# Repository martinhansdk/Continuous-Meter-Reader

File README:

Continuous Meter Reader
=======================

A little gadget that sits on your water or electricity meter and monitors it continuously.
The collected reading are presented on a mobile web page so that you can practice saving
ressources by answering questions like "How much water do I use when I take a shower?".

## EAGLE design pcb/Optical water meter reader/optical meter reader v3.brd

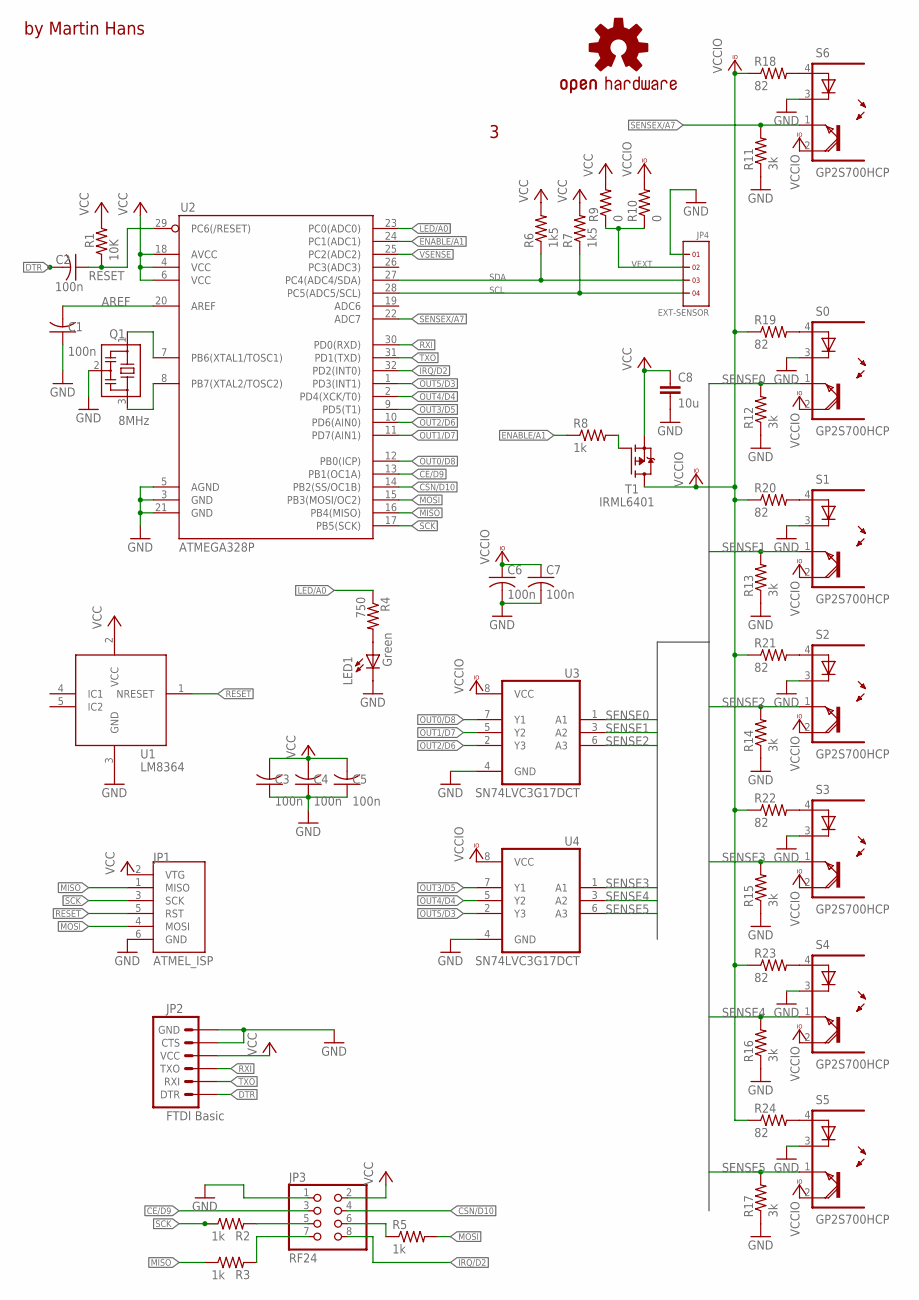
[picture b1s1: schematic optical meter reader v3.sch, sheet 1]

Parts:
C1, C2, C3, C4, C5, C6, C7: 100n; C0603
C8: 10u; C0603
JP1: ATMEL_ISP; 2X03
JP2: FTDI Basic; 1X06
JP3: RF24; 2X04
JP4: EXT-SENSOR; 1X4
LED1: Green; 0603-LED-ALT1
LOGO1: OSHW-LOGOL; OSHW-LOGO-L
Q1: 8MHz; CSTCE
R1: 10K; R0603
R2, R3, R5, R8: 1k; R0603
R4: 750; R0603
R6, R7: 1k5; R0603
R9, R10: 0; R0603
R11, R12, R13, R14, R15, R16, R17: 3k; R0603
R18, R19, R20, R21, R22, R23, R24: 82; R0603
S0, S1, S2, S3, S4, S5, S6: GP2S700HCP; SMD
T1: IRML6401; SOT23
U1: LM8364; SOT23-DBV
U2: ATMEGA328P; TQFP32-08
U3, U4: SN74LVC3G17DCT; SSOP08

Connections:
AREF: C1.2, U2.20 (AREF)
CE/D9: JP3.3, U2.13 (PB1(OC1A))
CSN/D10: JP3.4, U2.14 (PB2(SS/OC1B))
DTR: C2.2, JP2.1 (DTR)
ENABLE/A1: R8.1, U2.24 (PC1(ADC1)); also elsewhere on the board
GND: C1.1, C3.1, C4.1, C5.1, C6.2, C7.2, C8.2, JP1.6 (GND), JP2.5 (CTS), JP2.6 (GND), JP3.1, JP4.1, LED1.C, Q1.2, R11.1, R12.1, R13.1, R14.1, R15.1, R16.1, R17.1, S0.3 (C), S1.3 (C), S2.3 (C), S3.3 (C), S4.3 (C), S5.3 (C), S6.3 (C), U1.3 (GND), U2.3 (GND), U2.5 (AGND), U2.21 (GND), U3.4 (GND), U4.4 (GND); also elsewhere on the board
IRQ/D2: JP3.8, U2.32 (PD2(INT0))
LED/A0: R4.1, U2.23 (PC0(ADC0))
MISO: JP1.1 (MISO), R3.1, U2.16 (PB4(MISO))
MOSI: JP1.4 (MOSI), R5.2, U2.15 (PB3(MOSI/OC2))
unnamed: R19.2, S0.4 (A)
unnamed: R20.2, S1.4 (A)
unnamed: R21.2, S2.4 (A)
unnamed: R22.2, S3.4 (A)
unnamed: R23.2, S4.4 (A)
unnamed: R18.2, S6.4 (A)
unnamed: R8.2, T1.1 (G)
unnamed: R24.2, S5.4 (A)
unnamed: LED1.A, R4.2
unnamed: Q1.3, U2.8 (PB7(XTAL2/TOSC2))
unnamed: Q1.1, U2.7 (PB6(XTAL1/TOSC1))
unnamed: JP3.6, R5.1
unnamed: JP3.7, R3.2
unnamed: JP3.5, R2.2
OUT0/D8: U2.12 (PB0(ICP)), U3.7 (Y1); also elsewhere on the board
OUT1/D7: U2.11 (PD7(AIN1)), U3.5 (Y2)
OUT2/D6: U2.10 (PD6(AIN0)), U3.2 (Y3)
OUT3/D5: U2.9 (PD5(T1)), U4.7 (Y1)
OUT4/D4: U2.2 (PD4(XCK/T0)), U4.5 (Y2)
OUT5/D3: U2.1 (PD3(INT1)), U4.2 (Y3)
RESET: C2.1, JP1.5 (RST), R1.1, U1.1 (NRESET), U2.29 (PC6(/RESET))
RXI: JP2.3 (TXO), U2.30 (PD0(RXD))
SCK: JP1.3 (SCK), R2.1, U2.17 (PB5(SCK))
SCL: JP4.4, R7.1, U2.28 (PC5(ADC5/SCL))
SDA: JP4.3, R6.1, U2.27 (PC4(ADC4/SDA))
SENSE0: R12.2, S0.1 (EMI), U3.1 (A1); also elsewhere on the board
SENSE1: R13.2, S1.1 (EMI), U3.3 (A2)
SENSE2: R14.2, S2.1 (EMI), U3.6 (A3)
SENSE3: R15.2, S3.1 (EMI), U4.1 (A1)
SENSE4: R16.2, S4.1 (EMI), U4.3 (A2)
SENSE5: R17.2, S5.1 (EMI), U4.6 (A3)
SENSEX/A7: R11.2, S6.1 (EMI), U2.22 (ADC7)
TXO: JP2.2 (RXI), U2.31 (PD1(TXD))
VCC: C3.2, C4.2, C5.2, C8.1, JP1.2 (VTG), JP2.4 (VCC), JP3.2, R1.2, R6.2, R7.2, R9.2, T1.2 (S), U1.2 (VCC), U2.4 (VCC), U2.6 (VCC), U2.18 (AVCC); also elsewhere on the board
VCCIO: C6.1, C7.1, R10.2, R18.1, R19.1, R20.1, R21.1, R22.1, R23.1, R24.1, S0.2 (COL), S1.2 (COL), S2.2 (COL), S3.2 (COL), S4.2 (COL), S5.2 (COL), S6.2 (COL), T1.3 (D), U3.8 (VCC), U4.8 (VCC)
VEXT: JP4.2, R9.1, R10.1
VSENSE: U2.25 (PC2(ADC2)); also elsewhere on the board

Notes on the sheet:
by Martin Hans

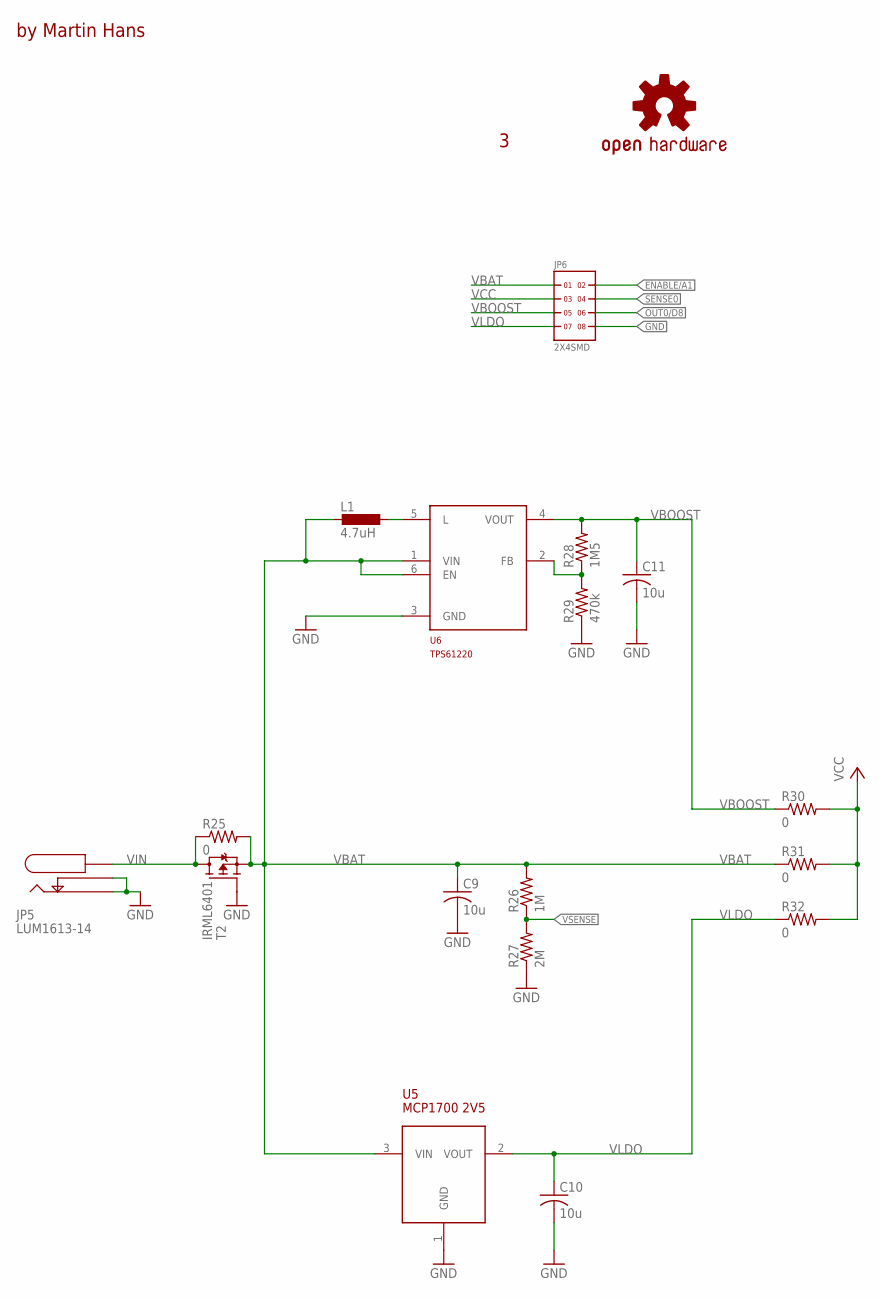
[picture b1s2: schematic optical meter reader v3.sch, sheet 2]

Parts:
C9, C10, C11: 10u; C0603
JP5: LUM1613-14; 1613-14
JP6: 2X4SMD; 2X4_SMD
L1: 4.7uH; EPL3015
LOGO2: OSHW-LOGOL; OSHW-LOGO-L
R25, R30, R31, R32: 0; R0603
R26: 1M; R0603
R27: 2M; R0603
R28: 1M5; R0603
R29: 470k; R0603
T2: IRML6401; SOT23
U5: MCP1700 2V5; SOT23
U6: TPS61220; DCK-R_PDSO_G6

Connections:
ENABLE/A1: JP6.2; also elsewhere on the board
FB: R28.1, R29.2, U6.2 (FB)
GND: C9.2, C10.2, C11.2, JP5.1 (SHIELD), JP5.2 (CONNECT), JP6.8, R27.1, R29.1, T2.1 (G), U5.1 (GND), U6.3 (GND); also elsewhere on the board
L: L1.P$2 (2), U6.5 (L)
OUT0/D8: JP6.6; also elsewhere on the board
SENSE0: JP6.4; also elsewhere on the board
VBAT: C9.1, JP6.1, L1.P$1 (1), R25.2, R26.2, R31.1, T2.2 (S), U5.3 (VIN), U6.1 (VIN), U6.6 (EN)
VBOOST: C11.1, JP6.5, R28.2, R30.1, U6.4 (VOUT)
VCC: JP6.3, R30.2, R31.2, R32.2; also elsewhere on the board
VIN: JP5.3@1 (CENTER), JP5.3@2 (CENTER), R25.1, T2.3 (D)
VLDO: C10.1, JP6.7, R32.1, U5.2 (VOUT)
VSENSE: R26.1, R27.2; also elsewhere on the board

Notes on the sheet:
by Martin Hans

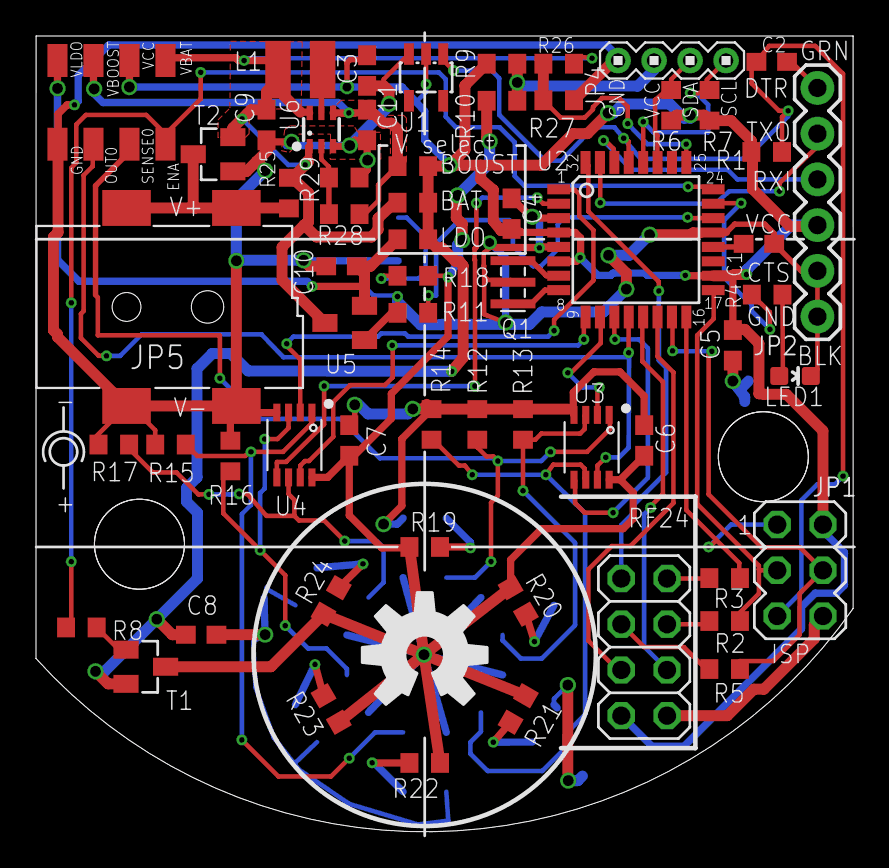
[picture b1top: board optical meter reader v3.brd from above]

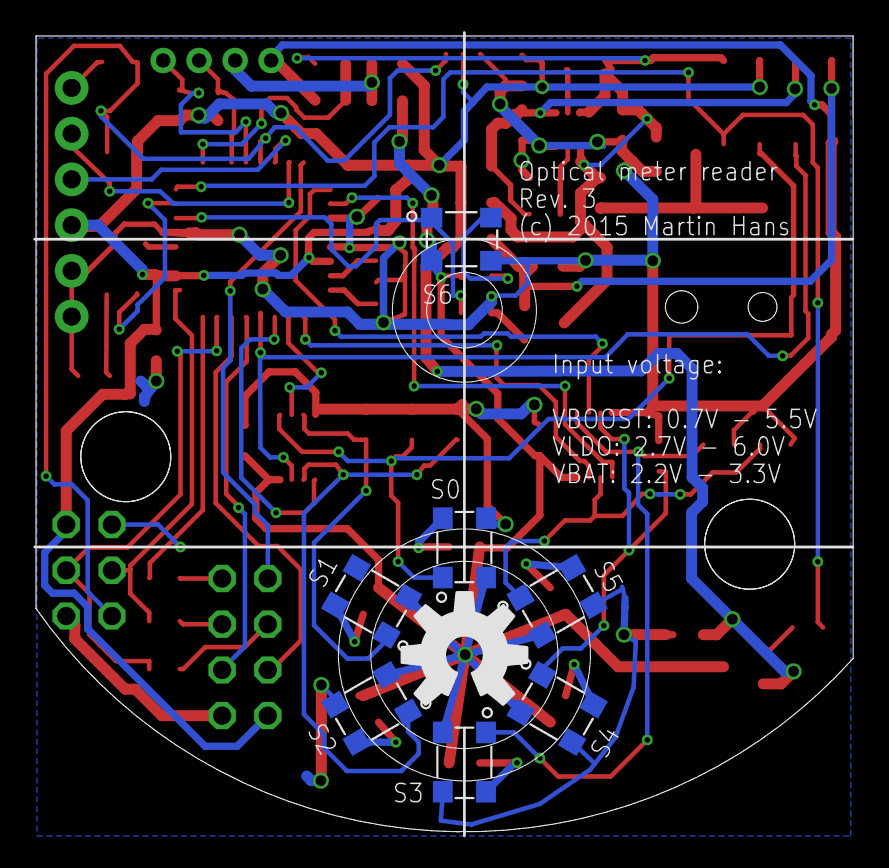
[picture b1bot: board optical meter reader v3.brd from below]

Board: 2 copper layers, 45.4 x 44.2 mm, 69 parts (8 on the bottom side), 53 nets.

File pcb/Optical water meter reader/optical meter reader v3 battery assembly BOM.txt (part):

Partlist exported from C:/Users/Hans/Documents/eagle/Optical water meter reader/optical meter reader v3.sch at 2016-04-21 11:47 AM

Part  Value          Device                    Package       Description                                                                                                                                                                                                        
C1    100n           C-USC0603                 C0603         CAPACITOR, American symbol                                                                                                                                                                                         
C2    100n           C-USC0603                 C0603         CAPACITOR, American symbol                                                                                                                                                                                         
C3    100n           C-USC0603                 C0603         CAPACITOR, American symbol                                                                                                                                                                                         
C4    100n           C-USC0603                 C0603         CAPACITOR, American symbol                                                                                                                                                                                         
C5    100n           C-USC0603                 C0603         CAPACITOR, American symbol                                                                                                                                                                                         
C6    100n           C-USC0603                 C0603         CAPACITOR, American symbol                                                                                                                                                                                         
C7    100n           C-USC0603                 C0603         CAPACITOR, American symbol                                                                                                                                                                                         
C8    10u            C-EUC0603                 C0603         CAPACITOR, European symbol                                                                                                                                                                                         
C9    10u            C-USC0603                 C0603         CAPACITOR, American symbol                                                                                                                                                                                         
C10   10u            C-USC0603                 C0603         CAPACITOR, American symbol                                                                                                                                                                                         
JP2   FTDI Basic     ARDUINO_SERIAL_PROGRAMPTH 1X06                                                                                                                                                                                                                             
JP3   RF24           PINHD-2X4                 2X04          PIN HEADER                                                                                                                                                                                                         
JP5   LUM1613-14     LUM1613-14                1613-14       Lumberg 1613 12 DC power connector                                                                                                                                                                                 
JP6   2X4SMD         2X4SMD                    2X4_SMD                                                                                                                                                                                                                          
LED1  Green          LED                       0603-LED-ALT1 LEDs                                                                                                                                                                                                               
LOGO1 OSHW-LOGOL     OSHW-LOGOL                OSHW-LOGO-L   Open Source Hardware Logo This logo indicates the piece of hardware it is found on incorporates a OSHW license and/or adheres to the definition of open source hardware found here: http://freedomdefined.org/OSHW 
LOGO2 OSHW-LOGOL     OSHW-LOGOL                OSHW-LOGO-L   Open Source Hardware Logo This logo indicates the piece of hardware it is found on incorporates a OSHW license and/or adheres to the definition of open source hardware found here: http://freedomdefined.org/OSHW 
Q1    8MHz           CSTCE                     CSTCE         Murata CSTCE                                                                                                                                                                                                       
R1    10K            R-US_R0603                R0603         RESISTOR, American symbol                                                                                                                                                                                          
R2    1k             R-US_R0603                R0603         RESISTOR, American symbol                                                                                                                                                                                          
R3    1k             R-US_R0603                R0603         RESISTOR, American symbol                                                                                                                                                                                          
R4    750            R-US_R0603                R0603         RESISTOR, American symbol                                                                                                                                                                                          
R5    1k             R-US_R0603                R0603         RESISTOR, American symbol                                                                                                                                                                                          
R8    1k             R-US_R0603                R0603         RESISTOR, American symbol                                                                                                                                                                                          
R12   3k             R-US_R0603                R0603         RESISTOR, American symbol                                                                                                                                                                                          
R13   3k             R-US_R0603                R0603         RESISTOR, American symbol                                                                                                                                                                                          
R14   3k             R-US_R0603                R0603         RESISTOR, American symbol                                                                                                                                                                                          
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
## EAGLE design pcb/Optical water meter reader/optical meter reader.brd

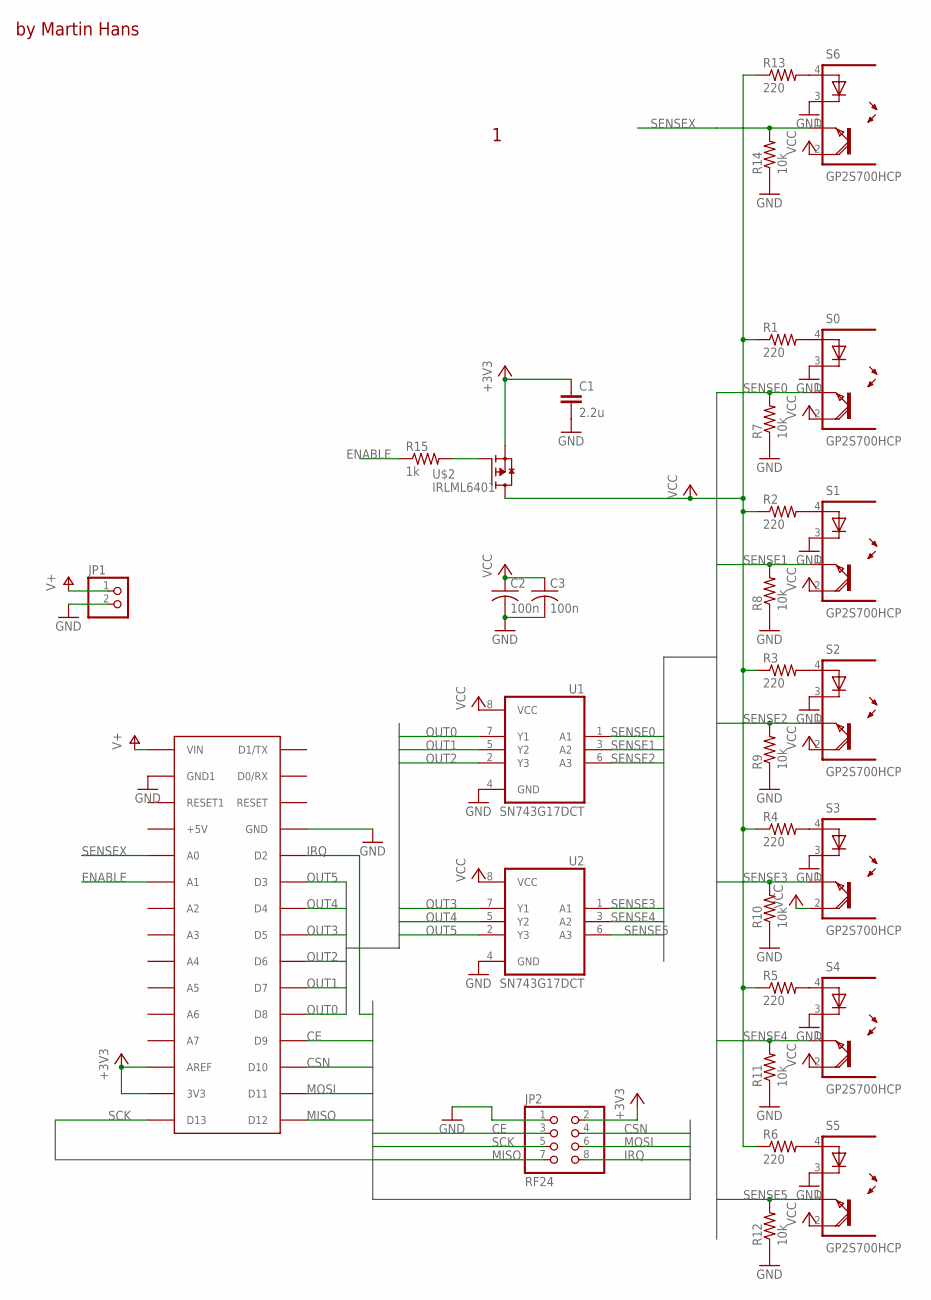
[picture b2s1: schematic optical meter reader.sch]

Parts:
C1: 2.2u; C0603
C2, C3: 100n; C0603
JP1: PINHD-1X2; 1X02
JP2: RF24; 2X04
R1, R2, R3, R4, R5, R6, R13: 220; R0603
R7, R8, R9, R10, R11, R12, R14: 10k; R0603
R15: 1k; R0603
S0, S1, S2, S3, S4, S5, S6: GP2S700HCP; SMD
U1, U2: SN743G17DCT; SSOP08
U$1: ARDUINONANO; PDIP-32
U$2: IRLML6401; SOT23

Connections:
+3V3: C1.1, JP2.2, U$1.3V3, U$1.AREF, U$2.2 (S)
CE: JP2.3, U$1.D9
CSN: JP2.4, U$1.D10
ENABLE: R15.1, U$1.A1
GND: C1.2, C2.2, C3.2, JP1.2, JP2.1, R7.1, R8.1, R9.1, R10.1, R11.1, R12.1, R14.1, S0.3 (C), S1.3 (C), S2.3 (C), S3.3 (C), S4.3 (C), S5.3 (C), S6.3 (C), U1.4 (GND), U2.4 (GND), U$1.GND, U$1.GND1
IRQ: JP2.8, U$1.D2
MISO: JP2.7, U$1.D12
MOSI: JP2.6, U$1.D11
unnamed: R1.2, S0.4 (A)
unnamed: R2.2, S1.4 (A)
unnamed: R3.2, S2.4 (A)
unnamed: R4.2, S3.4 (A)
unnamed: R5.2, S4.4 (A)
unnamed: R13.2, S6.4 (A)
unnamed: R15.2, U$2.1 (G)
unnamed: R6.2, S5.4 (A)
OUT0: U1.7 (Y1), U$1.D8
OUT1: U1.5 (Y2), U$1.D7
OUT2: U1.2 (Y3), U$1.D6
OUT3: U2.7 (Y1), U$1.D5
OUT4: U2.5 (Y2), U$1.D4
OUT5: U2.2 (Y3), U$1.D3
SCK: JP2.5, U$1.D13
SENSE0: R7.2, S0.1 (EMI), U1.1 (A1)
SENSE1: R8.2, S1.1 (EMI), U1.3 (A2)
SENSE2: R9.2, S2.1 (EMI), U1.6 (A3)
SENSE3: R10.2, S3.1 (EMI), U2.1 (A1)
SENSE4: R11.2, S4.1 (EMI), U2.3 (A2)
SENSE5: R12.2, S5.1 (EMI), U2.6 (A3)
SENSEX: R14.2, S6.1 (EMI), U$1.A0
V+: JP1.1, U$1.VIN
VCC: C2.1, C3.1, R1.1, R2.1, R3.1, R4.1, R5.1, R6.1, R13.1, S0.2 (COL), S1.2 (COL), S2.2 (COL), S3.2 (COL), S4.2 (COL), S5.2 (COL), S6.2 (COL), U1.8 (VCC), U2.8 (VCC), U$2.3 (D)

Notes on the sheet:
by Martin Hans

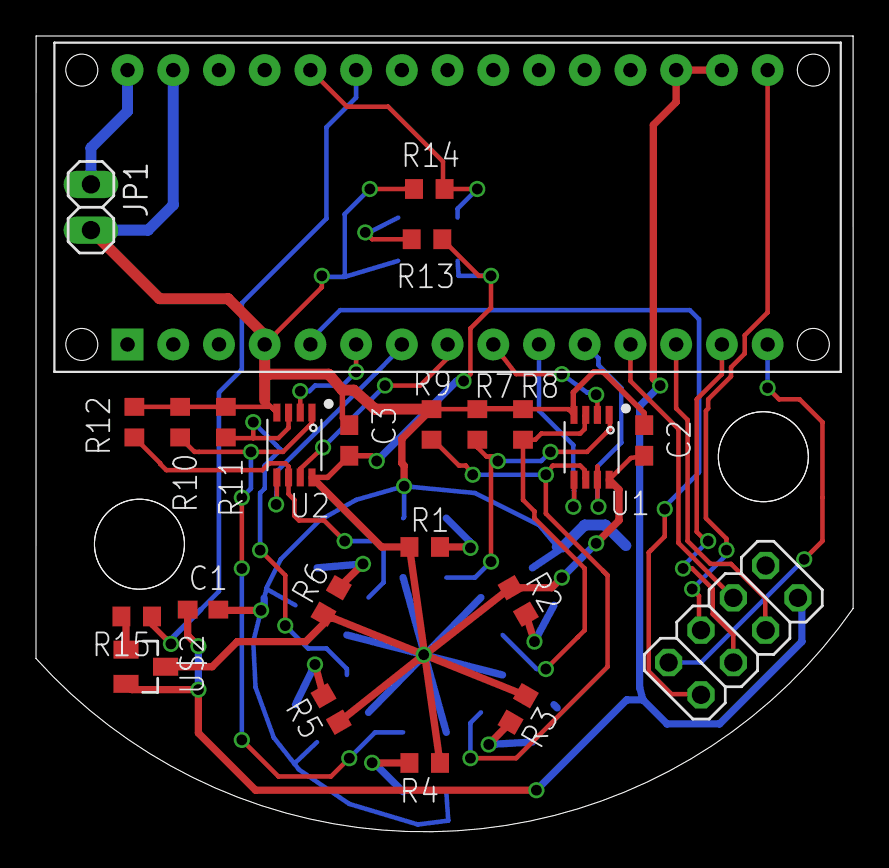
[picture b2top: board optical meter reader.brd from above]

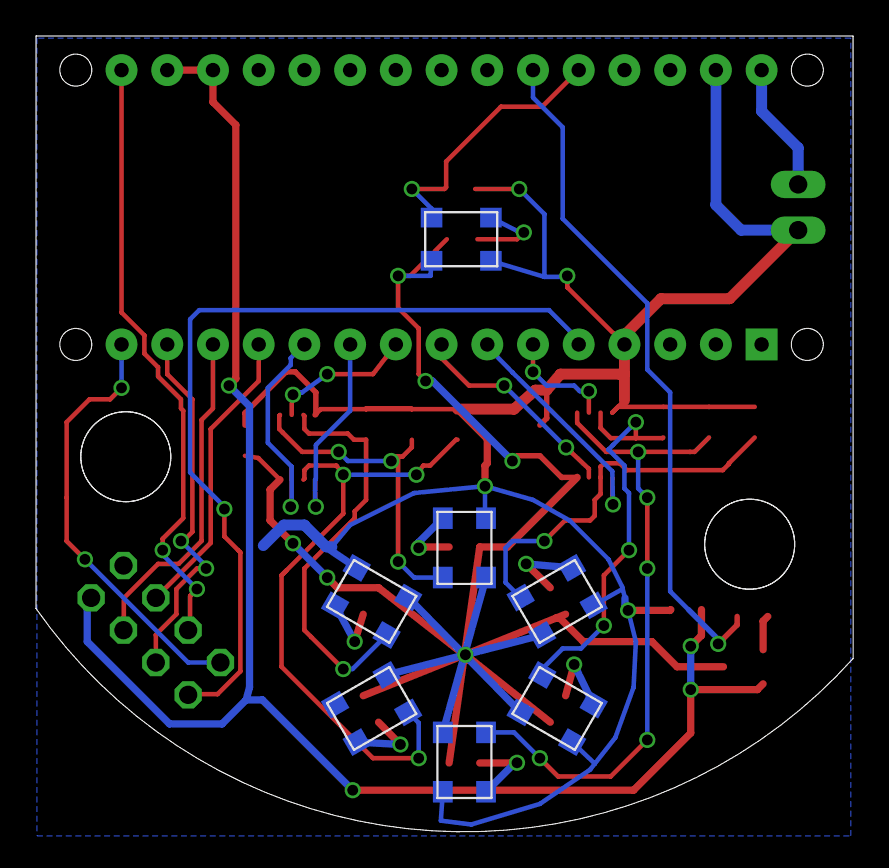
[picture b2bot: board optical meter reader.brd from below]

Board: 2 copper layers, 45.4 x 44.2 mm, 31 parts (7 on the bottom side), 32 nets.

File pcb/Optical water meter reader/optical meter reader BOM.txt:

Partlist exported from C:/Users/Hans/Documents/eagle/Optical water meter reader/optical meter reader.sch at 28-Aug-15 11:16 PM

Part Value       Device      Package Description                
C1   2.2u        C-EUC0603   C0603   CAPACITOR, European symbol 
C2   100n        C-USC0603   C0603   CAPACITOR, American symbol 
C3   100n        C-USC0603   C0603   CAPACITOR, American symbol 
JP1              PINHD-1X2   1X02    PIN HEADER                 
JP2  RF24        PINHD-2X4   2X04    PIN HEADER                 
R1   220         R-US_R0603  R0603   RESISTOR, American symbol  
R2   220         R-US_R0603  R0603   RESISTOR, American symbol  
R3   220         R-US_R0603  R0603   RESISTOR, American symbol  
R4   220         R-US_R0603  R0603   RESISTOR, American symbol  
R5   220         R-US_R0603  R0603   RESISTOR, American symbol  
R6   220         R-US_R0603  R0603   RESISTOR, American symbol  
R7   10k         R-US_R0603  R0603   RESISTOR, American symbol  
R8   10k         R-US_R0603  R0603   RESISTOR, American symbol  
R9   10k         R-US_R0603  R0603   RESISTOR, American symbol  
R10  10k         R-US_R0603  R0603   RESISTOR, American symbol  
R11  10k         R-US_R0603  R0603   RESISTOR, American symbol  
R12  10k         R-US_R0603  R0603   RESISTOR, American symbol  
R13  220         R-US_R0603  R0603   RESISTOR, American symbol  
R14  10k         R-US_R0603  R0603   RESISTOR, American symbol  
R15  1k          R-US_R0603  R0603   RESISTOR, American symbol  
S0   GP2S700HCP  GP2S700HCP  SMD                                
S1   GP2S700HCP  GP2S700HCP  SMD                                
S2   GP2S700HCP  GP2S700HCP  SMD                                
S3   GP2S700HCP  GP2S700HCP  SMD                                
S4   GP2S700HCP  GP2S700HCP  SMD                                
S5   GP2S700HCP  GP2S700HCP  SMD                                
S6   GP2S700HCP  GP2S700HCP  SMD                                
U$1  ARDUINONANO ARDUINONANO PDIP-32                            
U$2  IRLML6401   IRLML6401   SOT23                              
U1   SN743G17DCT SN743G17DCT SSOP08                             
U2   SN743G17DCT SN743G17DCT SSOP08

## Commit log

2012-03-23 Initial draft of the Comparator, Histogram and Meter classes.
2012-03-23 Added some tests for the metering classes. Nothing compiles yet.
2012-03-23 Added readme.
2012-03-26 Draft implementation of the comparator - unfinished.
2012-03-30 Comparator test now passes. Histogram test compiles but fails.
2012-05-05 HistogramTest now passes.
2012-05-05 Meter now passes its tests.
2012-05-06 reduced the memory consumption of the histogram
2012-05-06 Basic metering and automatic calibration now works.
2012-05-31 Added Meter class which can receive counts from a counter source which always starts from zero. The Meter class will then keep correct count even if the counter source starts over once in a while.
2012-05-31 Initial work on support for rrdtool.
2012-06-10 Switch to interrupt driven operation.
    Remove all floating point calculations from Meter class.
2012-06-10 Communication between board and node-js server works now.
    Basic HTML page shows count and allows doing measurements.
2012-06-10 Server is now an express app, which serves both the static HTML and the real time content.
2012-06-11 ignore npm installed modules
2012-06-11 Dynamically set the correct host for socket.io.
2015-08-16 The beginnings of a meter server
    Intended to both receive the meter updates from the meter reader
    devices, store the data in the database, serve the web apps and provide
    a json rest API.
2015-08-16 Add rickshaw to the static folder
2015-08-16 Simple class for optical sensors
    This is just an API experiment for now.
2015-08-16 Get current meter state from database on server start
2015-08-16 Started a react based current meter display.
2015-08-21 Basic streaming from the meter to the web client works
2015-08-27 Arduino will now send the updates using protobuf
2015-08-28 Convert to Arduino-Makefile and a layout based on Bare-Arduino-Project
2015-08-28 Receiving protobuf messages from the Arduino over serial port now works
2015-08-28 Assign timestamp to meter update event on reception
2015-08-28 Store incoming counter updates in the database
2015-08-28 Arduino stores series and meter id in EPROM. Series id is counted up on every boot.
2015-09-10 Support more than one type of message in the communication
    A top level message now contains one of several submessages.
    The Arduino code now sends through a stream without the use of a buffer.
    Added a config message type which is transmitted when the Arduino code
    starts.
2015-09-20 Adds config tool to configure nodes
    Adds unit tests form settings save and load.
    Adds unit test for C++ communication.
    Adds log message type.
    Both Arduino and go can now send and receive.
2015-09-20 Start calibration mode when requested by the config script.
    Store calibration in EEPROM when it is done.
    Change the serial speed to 57600 baud.
2015-09-26 Fix calibration of analog values
    It which went wrong due to an integer overflow in the calibration
    calculation on the Arduino.
2015-09-26 Add the arduino-mock library
    From https://github.com/ikeyasu/arduino-mock
2015-09-26 Adds a test for the OpticalSensor class
2015-09-26 Support digital sampling mode
    Allow switching sampling mode from the config tools and setting edge
    amounts.
2015-09-26 MeterServer now tries different serial port names to find the right one
2015-09-26 Always include our own test stubs if possible
2015-10-02 Add calibration of digital sensors
2015-10-02 Remove the manicbug version of the RF24 library.
2015-10-11 Include the RF24 from TMRh20
2015-10-12 Adds RadioMessageSender which adds a header and allows sending messages too long to fit in a single package
2015-10-22 Add radio receiver class that will assemble messages from multiple senders
2015-10-23 Allow sending of empty chunks
2015-10-31 Integrates wireless sending into the node.
    Adds RadioStation which will be the base station for the system.
    Moves things around a bit.
2015-11-01 Clean up: remove analog sensor support, run code formatter
2015-11-01 Add a travis CI configuration
2015-11-01 Fix command for installing dependencies in travis
2015-11-02 Refresh googlemock dependency
2015-11-02 Attempt to get the arduino libraries in a way that is compatible with travis ci
    Conflicts:
    .travis.yml
2015-11-02 Travis: install gcc-avr packages
    Conflicts:
    .travis.yml
2015-11-02 Travis: Add arduino to package list and remove manual installation of it
2015-11-03 Travis: allow steps to run even though previous steps have failed
2015-11-03 add googlemock submodule
2015-11-03 Format code
2015-11-03 Remove old submodule reference
2015-11-03 Travis: handle submodules manually
2015-11-04 Fix compile warning.
2015-11-04 Travis: Try building on trusty
2015-11-05 Travis: move back to vm based build to be able to use trusty
2015-11-05 Travis: update before apt-get install
2015-11-05 Travis: use -y to avoid questions from apt-get
2015-11-05 Fixes compile time warnings on tests
2015-11-05 Fix failing unittest.
2015-11-05 Adds the PCB schematic and layout files
2015-11-05 Add photo of water meter.
2015-11-05 Add photo of the PCB
2015-11-05 Write a proper README
2015-11-05 Remove obsolete python server code
2015-11-06 Remove remaining artifacts from analog sampling mode.
2015-11-06 Add power gating
    This only turns on the LEDs when sampling them. We sample the sensors
    once every 5ms and only turn on the LEDs for 50us each time giving us a
    duty cycle of 1% on the LEDs. This reduces power consumption from 95mA
    to 20mA.
2015-11-06 Power down the radio when it is not used.
    This only saves a small amount of power, about 25uA.
2015-11-06 Power off unneeded peripherals
    Turn off the ADC, TWI and Timer0 since they are not used. This saves
    about 0.9mA.
2015-11-06 fixup! Remove remaining artifacts from analog sampling mode.
2015-11-06 Enable sleep mode
    Using the least deep sleep mode, IDLE. The timer interrupt will wake up
    the CPU. This saves about 6 mA so the power consumption is now around
    12mA.
2015-11-07 Added database setup instructions.
2015-11-07 Implement SampleSender in go instead
    This removes python and the python protobuf plugin as a dependency.
    One less thing to get the right version of.
2015-11-09 Simplify build instructions for the go programs
2015-11-09 Add PDF of the board layout and a description in the README on how to use it to see if the board will fit a water meter
2015-11-09 Fix link to board layout PDF and clarify.
2015-11-10 Add sample output from calibration to the README
2015-11-10 Only insert rows in the database when there is an actual change.
2015-11-14 Update of UI. Update SampleSender.go to enable more meters to be sampled. Good for testing UI. Update MeterServer.go to give a better log message.
2015-11-14 See last commit message.
2015-11-15 Add API endpoint /api/values/#meterid which returns a json array of all measurement values for a given meter suitable for plotting. Add scale field to the meters database table so that all json can r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
2015-11-15 Move the database schema into it's own file and mention it in the README.
2015-11-15 More UI prettyfying Handle button state in main.js so that the graphs can update. Add JSON printout i graph area to show how that works.
    Next step is to use those data for something...
2015-11-15 UI additions.
2015-11-19 Update to show graphs of the meters. Big. bIg. BIG issues with D3, Richshar, Chart.js and many others. Finally found "canvasjs" and "React-ified" that one. Still little kinks with the date format. Wh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
2015-11-20 Change time returned from server to milleseconds. Javascript seems to like that better...
2016-04-29 Use a glob to find the serial port instead of a static list.
2016-04-29 Switch to v2 in the Makefile
2016-04-29 Fix glob pull request code.
2016-04-29 Remove test code
2016-04-29 Add instruction for how to initialize a fresh v2 board.
2016-04-29 Add documentation for PCB version 2
    Add -uncalibrate option to ConfigNode.go to make it easier to configure
    a board to have a full set of sensors.
2016-05-01 add v3 eagle files
2016-05-01 Organize information about the two PCB versions better.
2016-05-13 Fixes bug that caused the MeterServer to miscount when it rebooted
    Adds unittest for MeterStateHandler.Translate()
    Extracts interface from MeasurementStorer and renames MeterDB to
    PostgresMeterDB and makes it an implementation of that interface.
2018-11-05 Fix links to files in the repository
    Github changed the syntax for links and no longer allows spaces in the URL.
2018-11-05 Update dependency on uglify-js 2.6.0
    A security vulnerability exists in the previously used version: https://snyk.io/test/npm/uglify-js/2.2.5

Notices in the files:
pcb/Optical water meter reader/optical meter reader v3.brd:
(c) 2015 Martin Hans
parts and their libraries:
SparkFun-Aesthetics: Licensing: Creative Commons ShareAlike 4.0 International - https://creativecommons.org/licenses/by-sa/4.0
